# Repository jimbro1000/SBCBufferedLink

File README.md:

# Buffered Backplane Link for HD6309SBC #

This project defines a buffered interconnect between backplane panels
All lines are passed through a high speed bidirectional level shifter
to provide current buffering.

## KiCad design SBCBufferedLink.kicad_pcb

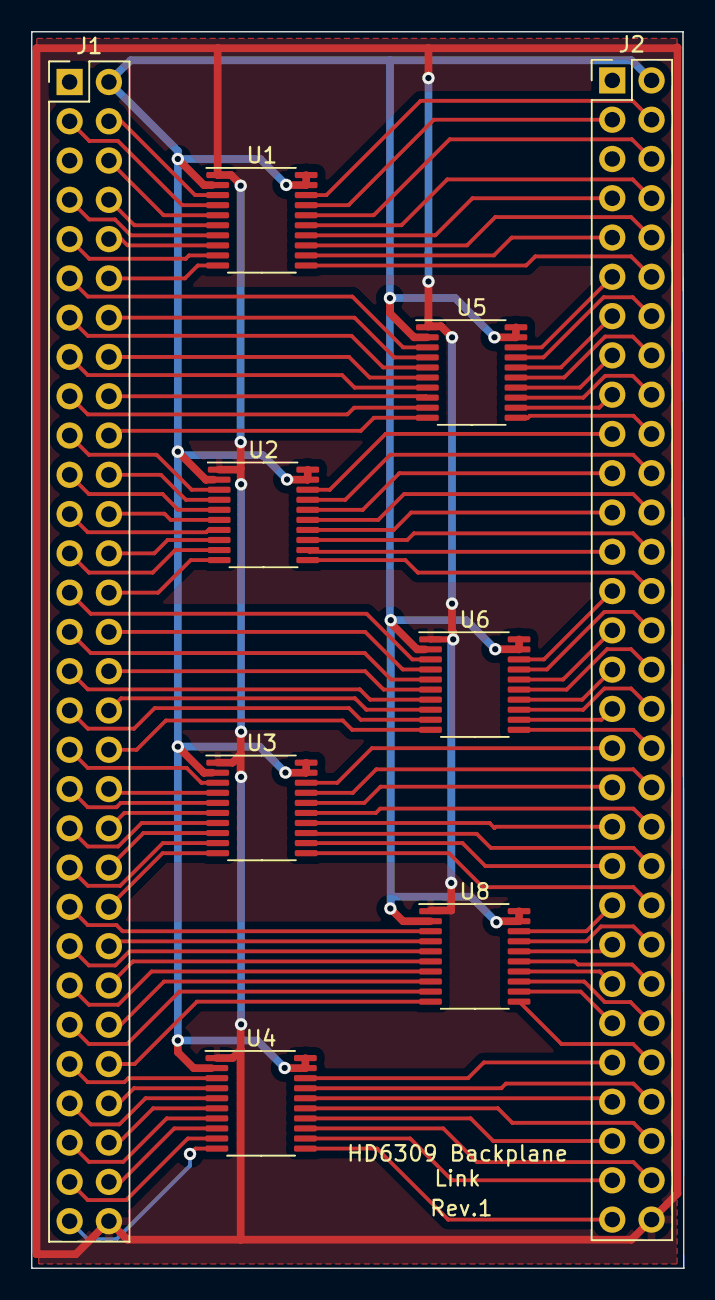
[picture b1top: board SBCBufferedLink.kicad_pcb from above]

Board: 2 copper layers, 42.2 x 80.0 mm, 9 parts (0 on the bottom side), 114 nets.

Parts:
J1: Left; PinHeader_2x30_P2.54mm_Vertical
J2: Right; PinHeader_2x30_P2.54mm_Vertical
U1, U2, U3, U4, U5, U6, U8: TSSOP-20_4.4x6.5mm_P0.65mm

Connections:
+5V: J1.2, J2.2, U1.2 (Vref_A), U1.19 (Vref_B), U1.20 (EN), U2.2 (Vref_A), U2.19 (Vref_B), U2.20 (EN), U3.2 (Vref_A), U3.19 (Vref_B), U3.20 (EN), U4.2 (Vref_A), U4.19 (Vref_B), U4.20 (EN), U5.2 (Vref_A), U5.19 (Vref_B), U5.20 (EN), U6.2 (Vref_A), U6.19 (Vref_B), U6.20 (EN), U8.2 (Vref_A), U8.19 (Vref_B), U8.20 (EN)
A0: J2.12, U1.11 (B8)
A0_LEFT: J1.12, U1.10 (A8)
A1: J2.14, U5.17 (B2)
A1_LEFT: J1.14, U5.4 (A2)
A2: J2.16, U5.15 (B4)
A2_LEFT: J1.16, U5.6 (A4)
A3: J2.18, U5.13 (B6)
A3_LEFT: J1.18, U5.8 (A6)
A4: J2.20, U5.11 (B8)
A4_LEFT: J1.20, U5.10 (A8)
A5: J2.22, U2.17 (B2)
A5_LEFT: J1.22, U2.4 (A2)
A6: J2.24, U2.15 (B4)
A6_LEFT: J1.24, U2.6 (A4)
A7: J2.26, U2.13 (B6)
A7_LEFT: J1.26, U2.8 (A6)
A8: J2.28, U2.11 (B8)
A8_LEFT: J1.28, U2.10 (A8)
A9: J2.30, U6.17 (B2)
A9_LEFT: J1.30, U6.4 (A2)
A10: J2.32, U6.15 (B4)
A10_LEFT: J1.32, U6.6 (A4)
A11: J2.34, U6.13 (B6)
A11_LEFT: J1.34, U6.8 (A6)
A12: J2.36, U6.11 (B8)
A12_LEFT: J1.36, U6.10 (A8)
A13: J2.38, U3.17 (B2)
A13_LEFT: J1.38, U3.4 (A2)
A14: J2.40, U3.15 (B4)
A14_LEFT: J1.40, U3.6 (A4)
A15: J2.42, U3.13 (B6)
A15_LEFT: J1.42, U3.8 (A6)
BA: J2.54, U4.17 (B2)
BA_LEFT: J1.54, U4.4 (A2)
BS: J2.56, U4.15 (B4)
BS_LEFT: J1.56, U4.6 (A4)
Clock3: J2.4, U1.18 (B1)
Clock3_LEFT: J1.4, U1.3 (A1)
Clock6: J2.6, U1.16 (B3)
Clock6_LEFT: J1.6, U1.5 (A3)
Clock24: J2.3, U1.17 (B2)
Clock24_LEFT: J1.3, U1.4 (A2)
D0: J2.11, U5.18 (B1)
D0_LEFT: J1.11, U5.3 (A1)
D1: J2.13, U5.16 (B3)
D1_LEFT: J1.13, U5.5 (A3)
D2: J2.15, U5.14 (B5)
D2_LEFT: J1.15, U5.7 (A5)
D3: J2.17, U5.12 (B7)
D3_LEFT: J1.17, U5.9 (A7)
D4: J2.19, U2.18 (B1)
D4_LEFT: J1.19, U2.3 (A1)
D5: J2.21, U2.16 (B3)
D5_LEFT: J1.21, U2.5 (A3)
D6: J2.23, U2.14 (B5)
D6_LEFT: J1.23, U2.7 (A5)
D7: J2.25, U2.12 (B7)
D7_LEFT: J1.25, U2.9 (A7)
E: J2.8, U1.15 (B4)
E_LEFT: J1.8, U1.6 (A4)
GND: J1.60, J2.60, U1.1 (GND), U2.1 (GND), U3.1 (GND), U4.1 (GND), U5.1 (GND), U6.1 (GND), U8.1 (GND)
MAPPED_MEM: J2.27, U6.18 (B1)
MAPPED_MEM_LEFT: J1.27, U6.3 (A1)
MRDY: J2.55, U4.14 (B5)
MRDY_LEFT: J1.55, U4.7 (A5)
NC1: J2.44, U3.11 (B8)
NC1_LEFT: J1.44, U3.10 (A8)
NC2: J2.53, U4.16 (B3)
NC2_LEFT: J1.53, U4.5 (A3)
NC3: J2.57, U4.12 (B7)
NC3_LEFT: J1.57, U4.9 (A7)
NC4: J2.58, U4.13 (B6)
NC4_LEFT: J1.58, U4.8 (A6)
NC5: J2.59, U4.11 (B8)
NC5_LEFT: J1.59, U4.10 (A8)
Q: J2.10, U1.13 (B6)
Q1: J2.31, U6.14 (B5)
Q1_LEFT: J1.31, U6.7 (A5)
Q2: J2.33, U6.12 (B7)
Q2_LEFT: J1.33, U6.9 (A7)
Q3: J2.35, U3.18 (B1)
Q3_LEFT: J1.35, U3.3 (A1)
Q4: J2.37, U3.16 (B3)
Q4_LEFT: J1.37, U3.5 (A3)
Q5: J2.39, U3.14 (B5)
Q5_LEFT: J1.39, U3.7 (A5)
Q6: J2.41, U3.12 (B7)
Q6_LEFT: J1.41, U3.9 (A7)
Q7: J2.43, U8.18 (B1)
Q7_LEFT: J1.43, U8.3 (A1)
Q8: J2.45, U8.16 (B3)
Q8_LEFT: J1.45, U8.5 (A3)
Q_LEFT: J1.10, U1.8 (A6)
ROM/~RAM: J2.29, U6.16 (B3)
ROM/~RAM_LEFT: J1.29, U6.5 (A3)
R/~W: J2.49, U8.12 (B7)
R/~W_LEFT: J1.49, U8.9 (A7)
~DMA: J2.47, U8.14 (B5)
~DMA_LEFT: J1.47, U8.7 (A5)
~E: J2.7, U1.14 (B5)
~E_LEFT: J1.7, U1.7 (A5)
~FIRQ: J2.50, U8.13 (B6)
~FIRQ_LEFT: J1.50, U8.8 (A6)
~HALT: J2.51, U4.18 (B1)
~HALT_LEFT: J1.51, U4.3 (A1)
~IRQ: J2.52, U8.11 (B8)
~IRQ_LEFT: J1.52, U8.10 (A8)
~NMI: J2.48, U8.15 (B4)
~NMI_LEFT: J1.48, U8.6 (A4)
~Q: J2.9, U1.12 (B7)
~Q_LEFT: J1.9, U1.9 (A7)
~RESET: J2.46, U8.17 (B2)
~RESET_LEFT: J1.46, U8.4 (A2)

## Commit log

2023-04-24 add board edge
2023-04-24 add preliminary render
2023-04-24 complete tracing
